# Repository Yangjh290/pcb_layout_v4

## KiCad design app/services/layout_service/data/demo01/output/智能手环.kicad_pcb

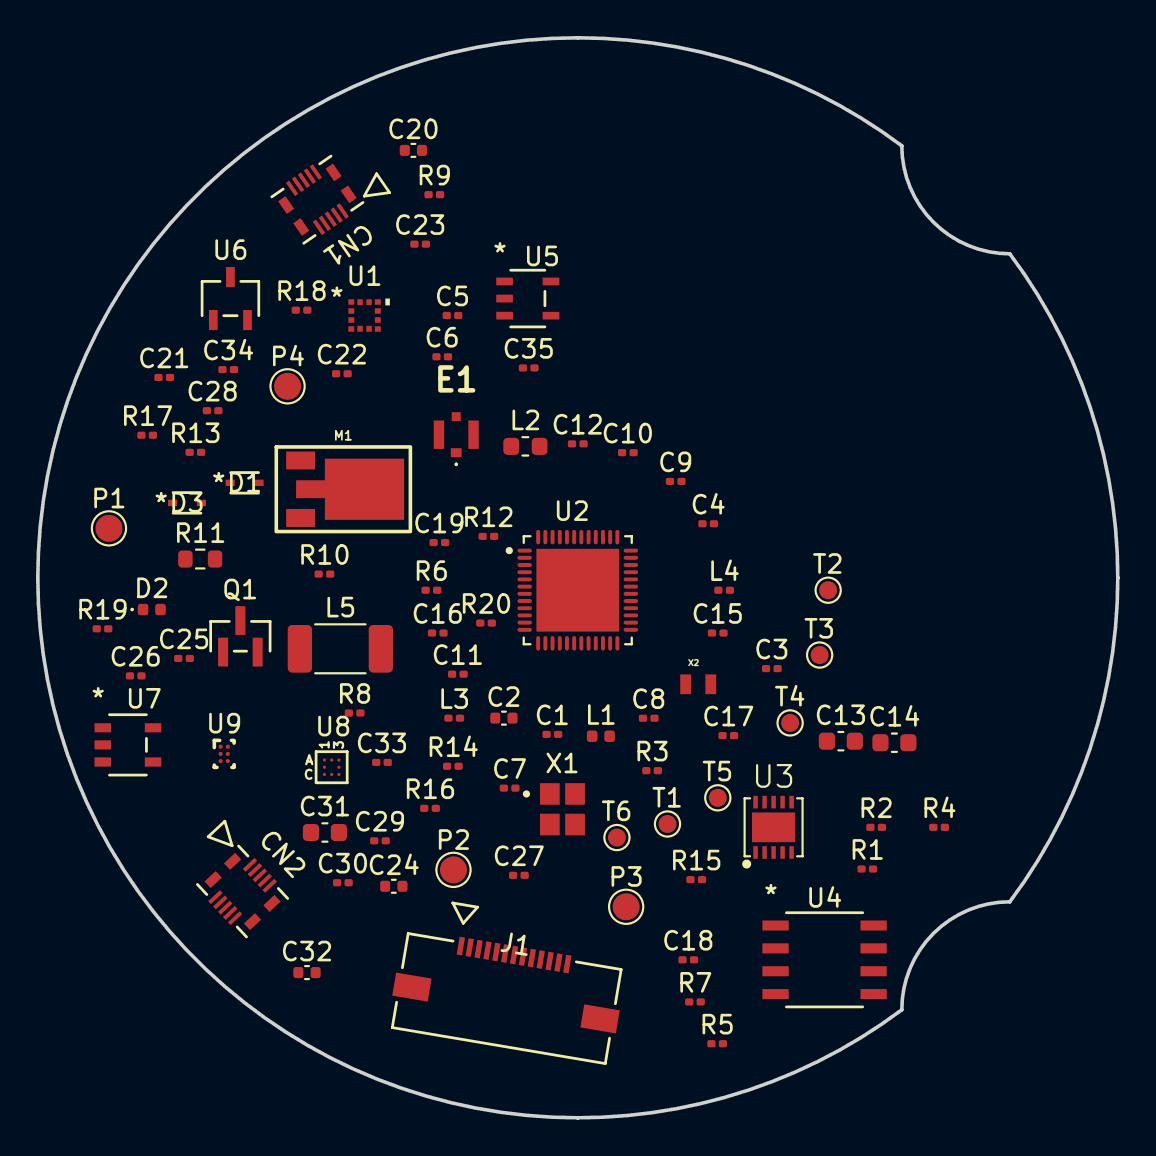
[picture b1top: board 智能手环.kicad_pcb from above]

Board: 2 copper layers, 60.0 x 60.0 mm, 90 parts (0 on the bottom side), 66 nets, no tracks yet.

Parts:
C1, C25, C29: 1uF; C_0201_0603Metric
C2, C20, C24, C32: 4.7uF; C_0402_1005Metric
C3, C5, C6, C9, C18, C19, C21, C22, C23, C26, C27, C28, C30, C33, C34, C35: 0.1uF; C_0201_0603Metric
C4, C8, C15: 12pF; C_0201_0603Metric
C7, C10: 20PF; C_0201_0603Metric
C11: 100pF; C_0201_0603Metric
C12, C17: NC; C_0201_0603Metric
C13, C14, C31: 2.2uF; C_0603_1608Metric
C16: 0.8pF; C_0201_0603Metric
CN1, CN2: CON_559099872
D1, D3: ZHCS350TA; CR_350TA_DIO
D2: BTR04F15; D_0402_1005Metric
E1: RECE.20449.001E.01; RECE20449001E01
J1: CON_5051101392_MOL
L1: 15nH; L_0402_1005Metric
L2: 10uH; L_0603_1608Metric
L3: 3.9nH; L_0201_0603Metric
L4: NC; L_0201_0603Metric
L5: LQH2MCN100M52; L_2010_5025Metric
M1: Z3OC1T8219731
P1: VUSB; TestPoint_Pad_D1.5mm
P2: B+; TestPoint_Pad_D1.5mm
P3: GND; TestPoint_Pad_D1.5mm
P4: B-; TestPoint_Pad_D1.5mm
Q1: MMBT3904; SOT-23_MCC
R1, R2, R3: 330R; R_0201_0603Metric
R4, R5, R6, R7, R8: 10K; R_0201_0603Metric
R9: NC; R_0201_0603Metric
R10: 16K_1%; R_0201_0603Metric
R11: 25.5R; R_0603_1608Metric
R12: 2K; R_0201_0603Metric
R13: 1M; R_0201_0603Metric
R14: 810K 1%; R_0201_0603Metric
R15: 155K 1%; R_0201_0603Metric
R16: 560K; R_0201_0603Metric
R17, R18, R19: 1M_1%; R_0201_0603Metric
R20: 196K_1%; R_0201_0603Metric
T1: RX; TestPoint_Pad_D1.0mm
T2: TX; TestPoint_Pad_D1.0mm
T3: SWDIO; TestPoint_Pad_D1.0mm
T4: SWDCLK; TestPoint_Pad_D1.0mm
T5: 3V3; TestPoint_Pad_D1.0mm
T6: GND; TestPoint_Pad_D1.0mm
U1: KX122_1037; LGA12_2X2_KNX
U2: NRF52832; QFN40P600X600X90-49N
U3: IQS263; IQS263B
U4: W25X40CLSNIG
U5: XC6215B332MR-G; XC6215B332MR_G
U6: XC61CC3302MR-G; XC61C_SOT-23_TOR
U7: XC6802A42XMR-G; SOP_XC6802_TOR
U8: AK09911C; WL-CSPBGA8_1p2x1p2x0p5_AKM
U9: TPS61046; YFF0006AAAA
X1: CRYSTAL1-4/SM; XTAL_FA-20H_32.0000MF12Y-W3
X2: 32.768KHz; XTAL_ECS-.327-12.5-12-TR

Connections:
3V3: C2.2, C3.2, C6.1, C13.1, C18.1, C19.2, C20.1, C21.1, C26.2, C27.2, C33.1, CN2.5, J1.4 (VDD), R4.2, R5.1, R7.1, R8.1, T5.1 (TP), U1.7 (VDD), U2.13 (VDD1), U2.36 (VDD2), U2.48 (VDD3), U3.4 (VDDHI), U4.8 (VCC), U5.5 (VOUT), U8.A1 (VDD), U8.C1 (V1.8)
AC_CLK: U1.12 (SCLK/SCL), U2.7 (P0.05/AIN3)
AC_CS#: U1.10 (nCS), U2.8 (P0.06)
AC_INT1: U1.5 (INT1), U2.10 (P0.08)
AC_MISO: U1.1 (SDO/ADDR), U2.5 (P0.03/AIN1)
AC_MOSI: U1.2 (SDI/SDA), U2.4 (P0.02/AIN0)
BAT_P: C35.1, R19.2, R20.1, U2.6 (P0.04/AIN2)
CLK: R6.1, T4.1 (TP), U2.25 (SWDCLK)
C_STATUS: R8.2, U2.17 (P0.14), U7.1 (~CHG~)
DIO: T3.1 (TP), U2.26 (SWDIO)
FLASH_CS: U2.20 (P0.17), U4.1 (~CS~)
GND: C1.1, C2.1, C3.1, C4.2, C5.2, C6.2, C7.1, C8.2, C9.2, C10.1, C11.2, C12.2, C13.2, C14.2, C16.2, C17.2, C18.2, C19.1, C20.2, C21.2, C22.1, C23.1, C24.2, C25.2, C26.1, C27.1, C29.2, C30.1, C31.2, C32.1, C33.2, C34.2, C35.2, CN1.9, CN1.10, CN2.9, CN2.10, D2.1, J1.5 (IM1), J1.12 (VSS), L4.1, M1.3 (GND), P3.1 (TP), P4.1 (TP), Q1.2 (E), R6.2, R10.2, R13.2, R15.2, R16.2, R18.2, R20.2, T6.1 (TP), U1.4 (TRIG), U1.8 (GND1), U1.9 (GND2), U2.31 (VSS1), U2.45 (VSS2), U2.49 (VSS3), U3.1 (GND), U3.11 (GND1), U4.4 (GND), U5.2 (GND), U6.2 (VSS), U7.2 (VSS), U8.B1 (VSS), U9.A2 (GND), X1.2, X1.4
HR_EN2: CN2.4, U2.21 (P0.18)
HR_INT: CN2.3, U2.22 (P0.19)
INT: U2.15 (P0.12), U8.A3 (INT)
MISO: U2.37 (P0.25), U4.2 (DO)
MOSI: J1.11 (D1), U2.38 (P0.26), U4.5 (DI)
MOTOR_DRV: R12.1, U2.14 (P0.11)
unnamed: C15.1, L3.2, L4.2
unnamed: C15.2, C17.1, E1.1
unnamed: C25.1, D1.2 (CATHODE), U7.4 (VIN)
unnamed: C28.2, D3.1 (ANODE), M1.2, Q1.3 (C)
unnamed: C28.1, D3.2 (CATHODE), M1.1, R11.2
unnamed: J1.6 (IREF), R16.1
unnamed: C32.2, J1.3 (VCOMH)
unnamed: C30.2, C31.1, J1.2 (VPP), R14.2, U9.C2 (VOUT)
unnamed: L1.2, L2.1
unnamed: Q1.1 (B), R12.2, R13.1
unnamed: C5.1, U1.3 (IO_VDD)
unnamed: C16.1, L3.1, U2.30 (ANT)
unnamed: L2.2, U2.47 (DCC)
unnamed: C9.1, U2.1 (DEC1)
unnamed: C12.1, U2.32 (DEC2)
unnamed: C11.1, U2.33 (DEC3)
unnamed: C1.2, L1.1, U2.46 (DEC4)
unnamed: C7.2, U2.2 (P0.00/XL1), X2.2
unnamed: C10.2, U2.3 (P0.01/XL2), X2.1
unnamed: C8.1, U2.34 (XC1), X1.3
unnamed: C4.1, U2.35 (XC2), X1.1
unnamed: R1.2, U3.2 (CRX1)
unnamed: R3.2, U3.3 (CRX2)
unnamed: R2.1, U3.9 (CRX3)
unnamed: C14.1, U3.5 (VREG)
unnamed: R5.2, U4.7 (~HOLD~)
unnamed: R7.2, U4.3 (~WP~)
unnamed: C23.2, R9.1, U5.3 (CE), U6.1 (VOUT)
unnamed: R10.1, U7.5 (ISEN)
unnamed: R14.1, R15.1, U9.B1 (FB)
unnamed: L5.2, U9.B2 (SW)
OLED_A0: J1.9 (DC), U2.41 (P0.29/AIN5)
OLED_CS: J1.7 (CS), U2.43 (P0.31/AIN6)
OLED_EN1: U2.16 (P0.13), U9.C1 (EN)
OLED_RES: J1.8 (RES), U2.42 (P0.30/AIN6)
POWER_UP: C34.1, R17.2, R18.1, U2.18 (P0.15)
RDY: R4.1, U2.24 (P0.21/RESET), U3.6 (RDY)
RX: T1.1 (TP), U2.28 (P0.23)
RX1: CN1.1, R1.1
RX2: CN1.2, R3.1
RX3: CN1.3, R2.2
SCL: CN2.2, U2.11 (P0.09), U3.8 (SCL), U8.B3 (SCL)
SDA: CN2.1, U2.12 (P0.10), U3.7 (SDA), U8.C3 (SDA)
SPI_CLK: J1.10 (D0), U2.39 (P0.27), U4.6 (CLK)
TX: T2.1 (TP), U2.27 (P0.22)
TX0: CN1.4, U3.10 (CTX/PO)
VBAT: C22.2, C24.1, C29.1, CN2.6, CN2.7, L5.1, P2.1 (TP), R9.2, R11.1, R19.1, U5.1 (VDD), U6.3 (VIN), U7.3 (BAT), U9.A1 (VIN)
VUSB: D1.1 (ANODE), D2.2, P1.1 (TP), R17.1

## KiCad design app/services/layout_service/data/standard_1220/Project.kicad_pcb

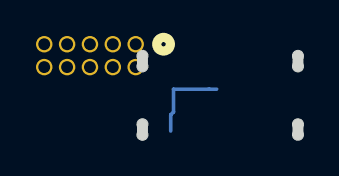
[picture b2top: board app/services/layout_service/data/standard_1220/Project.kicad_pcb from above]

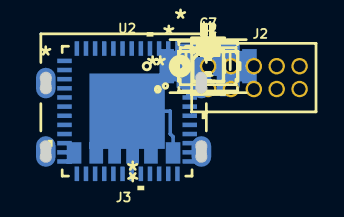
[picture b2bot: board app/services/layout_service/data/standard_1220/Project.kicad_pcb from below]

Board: 2 copper layers, 48 parts (48 on the bottom side), 25 nets.

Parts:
C1, C2: 1 uF; C_0603_1608Metric
C3: 220nF; C_0402_1005Metric
C4: 1uF; C_0402_1005Metric
C6: 0.47 uF; C_0402_1005Metric
C7: SM712-02HTG; SOT23-3_LTF
C8, C13: 10 pF; 0402C
C9, C10, C11, C15: 0.1uF; 0402C
C12, C17: 12 pF; 0402C
C14: 1uF; 0402C
C16, C18: 10uF; 0603C
D1: MMSZ5231BT1G; SOD-123_ONS
D2: PMEG3050EP,115; SDO_CFP5_SOD128_NEX
I1: STC3117IJT; BGA9C40P3X3_146X156X66
J2: M50-3500542; M50_3500542
J3: 2171750001; 2171750001_MOL
Q1: DMG2305UX-7; SOT-23_DIO
Q2: MMST3906-7-F; SOT-323_DIO
R1: 10k; R_0603_1608Metric
R2, R3: 1K; R_0402_1005Metric
R4, R5, R6: 10K; R_0402_1005Metric
R7: 10m; R_0402_1005Metric
R8, R10, R12: 10k; R_0402_1005Metric
R9: 300; R_0402_1005Metric
R11: 1k; R_0402_1005Metric
R13, R14, R15, R16: 4.7k; 0402R
R17: 1k; 0402R
R18: 330; 0402R
R19: 10k; 0402R
S1: B3U-1000P
U1: ADP122AUJZ-3.3-R7; UJ_5_ADI
U2: ATSAMD21G18A-MUT; QFN48_7X7MC_MCH
X1: 12 MHz; ABM8G_12_000MHZ_B4Y_T
X2: 32.768 kHz; ABS05_32_768KHZ_T

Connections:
+BATT: C4.1, I1.C2 (VCC), R3.1
/BATD: I1.B1 (BATD), R2.1
GND: C1.2, C2.2, C3.2, C4.2, C6.2, C7.3, C8.2, C9.2, C10.2, C11.2, C12.2, C13.2, C14.2, C15.2, C16.2, C17.2, C18.2, I1.A3 (GND), J2.3, J2.5, J3.A12 (GND), J3.B12 (GND), R7.2, R12.1, S1.1, U1.2 (GND), U2.5 (GNDANA), U2.18 (GND), U2.35 (GND), U2.42 (GND), U2.49 (EP_GND), X1.2 (GND_1), X1.4 (GND_2)
I2C_SCL: I1.B2 (SCL), R5.2, U2.22 (PA13)
I2C_SDA: I1.A2 (SDA), R6.2, U2.21 (PA12)
KLT0: J3.A5 (CC1), U2.15 (PA10)
KLT1: J3.B5 (CC2), U2.14 (PA09)
KLT2: I1.A1 (CD), U2.13 (PA08)
KLT3: I1.B3 (CS), U2.12 (PA07)
KLT4: I1.C3 (ALM), R4.2, U2.11 (PA06)
KLT5: C7.1, U2.10 (PA05)
KLT6: C7.2, C12.1, U2.1 (PA00), X2.1
unnamed: R9.1, R11.2
unnamed: D2.1 (K), Q1.3 (D), Q2.2 (EMITTER), R9.2, R10.2
unnamed: C3.1, I1.C1 (VIN), R3.2
unnamed: Q1.1 (G), R8.2
unnamed: Q2.1 (BASE), R11.1
unnamed: Q2.3 (COLLECTOR), R8.1, R10.1, R12.2
unnamed: R2.2, R7.1
unnamed: R18.2, S1.2
unnamed: R1.2, U1.3 (EN)
unnamed: C14.1, U2.43 (VDDCORE)
VBUS: J3.A9 (VBUS), J3.B9 (VBUS)
VIN0: C2.1, R1.1, U1.1 (IN)
VOUT1: C1.1, C6.1, C9.1, C10.1, C11.1, C16.1, C18.1, J2.1, Q1.2 (S), R4.1, R5.1, R6.1, R13.2, R14.2, R15.2, R16.2, R17.2, R19.2, U1.5 (OUT), U2.6 (VDDANA), U2.17 (VDDIO), U2.36 (VDDIO), U2.44 (VDDIN)

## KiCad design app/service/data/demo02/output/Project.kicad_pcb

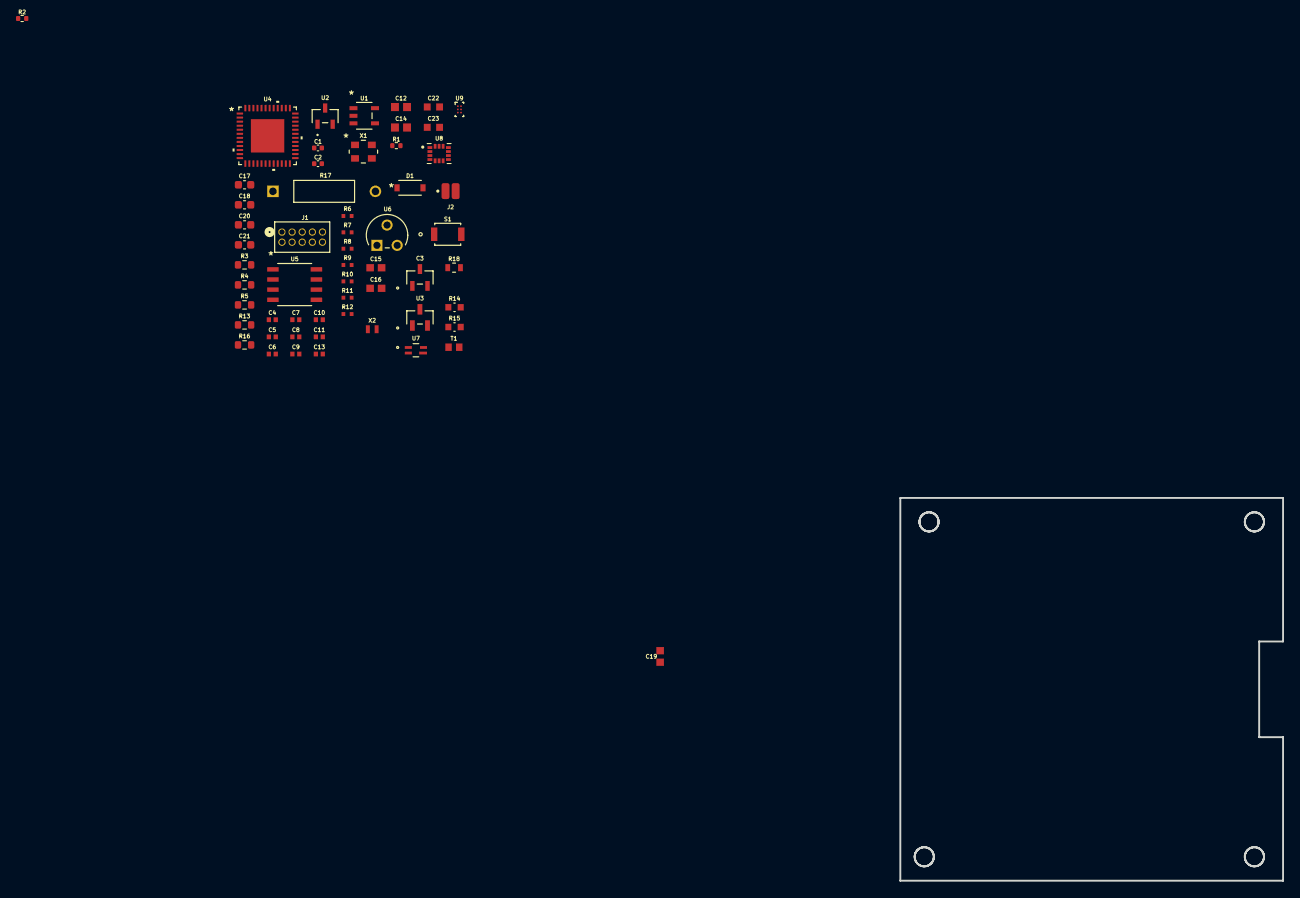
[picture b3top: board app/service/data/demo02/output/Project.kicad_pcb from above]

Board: 2 copper layers, 48.0 x 48.0 mm, 57 parts (0 on the bottom side), 27 nets, no tracks yet.

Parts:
C1, C2: 1uF; C_0402_1005Metric
C3: SM712-02HTG; SOT23-3_LTF
C4, C9: 10 pF; 0402C
C5, C6, C7, C11: 0.1uF; 0402C
C8, C13: 12 pF; 0402C
C10: 1uF; 0402C
C12, C14: 10uF; 0603C
C15, C19: 0.1uF; YAG_CC0603_YAG
C16: 0.01uF; YAG_CC0603_YAG
C17: 0.01uF; C_0603_1608Metric
C18: 1uF; C_0603_1608Metric
C20, C21: 0.1 uF; C_0603_1608Metric
C22, C23: 1uF; CAP_CL10A105KB8NNN_SAM
D1: KDZVTR6.2B; DIO_KDZLVTF100_ROM
J1: M50-3500542; M50_3500542
J2: NATTREY; SolderWirePad_1x02_SMD_1x2mm
R1: 210K; R_0402_1005Metric
R2: 40K; R_0402_1005Metric
R3: 33K; R_0603_1608Metric
R4: 1K; R_0603_1608Metric
R5: 100K; R_0603_1608Metric
R6, R7, R8, R9: 4.7k; 0402R
R10: 1k; 0402R
R11: 330; 0402R
R12: 10k; 0402R
R13: 75R; R_0603_1608Metric
R14, R15: 2.2K; RC0603N_YAG
R16: 10k; R_0603_1608Metric
R17: 6K; CMF55_VIS
R18: 1.35K; RES_RN73R_1J_KOA
S1: B3U-1000P
T1: Thermistor_NTC; TRES_NCP18XH103F03RB_MUR
U1: AP7366-W5-7; SOT25_DIO
U2: DRDC3105F-7; SOT23_MMBT2222A_NEX
U3: TCM809RVNB713; SOT-23_MC_MCH
U4: ATSAMD21G18A-MUT; QFN48_7X7MC_MCH
U5: MX25L4006EM2I-12G; SOIC8_SOP8L_MAC
U6: LM35DZ/NOPB; Z03A
U7: VEML6040A3OG; LED_VEML6040A3OG_VIS
U8: ISM330DHCXTR; PQFN50P250X300X86-14N
U9: BQ25101YFPR; YFP0006AFAV
X1: 12 MHz; ABM8G_12_000MHZ_B4Y_T
X2: 32.768 kHz; ABS05_32_768KHZ_T

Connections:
GND: C1.2, C2.2, C3.3, C4.2, C5.2, C6.2, C7.2, C8.2, C9.2, C10.2, C11.2, C12.2, C13.2, C14.2, C15.2, C16.2, C17.2, C19.2, C20.2, C21.2, C22.2, C23.2, D1.1, J1.3, J1.5, J2.2, R2.2, R3.2, R5.2, R16.2, R17.2, R18.2, S1.1, T1.2, U1.2 (GND), U2.2 (GND), U3.2 (GND), U4.5 (GNDANA), U4.18 (GND), U4.35 (GND), U4.42 (GND), U4.49 (EP_GND), U5.4 (GND), U6.3 (GND), U7.1 (GND), U8.6 (GND), U8.7 (GND), U9.C2 (VSS), X1.2 (GND_1), X1.4 (GND_2)
I2C_SCL: R9.1, R15.2, U4.26 (PA17), U7.3 (SCL), U8.13 (SCL)
I2C_SDA: R6.1, R14.2, U4.25 (PA16), U7.2 (SDA), U8.14 (SDA)
KLT0: R16.1, U4.16 (PA11), U8.4 (INT1)
KLT1: U4.15 (PA10), U8.9 (INT2)
KLT2: U4.14 (PA09), U5.5 (SI/SIO0)
KLT3: U4.13 (PA08), U5.6 (SCLK)
KLT4: U4.12 (PA07), U5.7 (HOLD#)
KLT5: C3.1, U4.11 (PA06)
KLT6: C3.2, U4.10 (PA05)
KLT7: C8.1, C18.1, U4.1 (PA00), X2.1
unnamed: C18.2, R13.2
unnamed: R3.1, R4.1, U2.1 (IN)
unnamed: R11.2, S1.2
unnamed: R1.2, R2.1, U1.4 (ADJ)
unnamed: R5.1, U3.3 (*RESET)
unnamed: C10.1, U4.43 (VDDCORE)
unnamed: R13.1, U6.2 (Vout)
unnamed: R17.1, U9.C1 (CHG_N)
unnamed: R18.1, U9.B2 (ISET)
unnamed: T1.1, U9.B1 (TS)
VDD: C19.1, R14.1, R15.1, U3.1 (VDD), U7.4 (VDD)
VIN: C22.1, U9.A2 (IN)
VOUT: C23.1, J2.1, U9.A1 (OUT)
VOUT1: C1.1, R4.2, U1.1 (IN), U1.3 (EN)
VOUT2: C2.1, R1.1, U1.5 (OUT)
VOUT3: C5.1, C6.1, C7.1, C12.1, C14.1, C15.1, C16.1, C17.1, C20.1, C21.1, D1.2, J1.1, R6.2, R7.2, R8.2, R9.2, R10.2, R12.2, U2.3 (OUT), U4.6 (VDDANA), U4.17 (VDDIO), U4.36 (VDDIO), U4.44 (VDDIN), U5.8 (VCC), U6.1 (+VS), U8.1 (SDO/SA0), U8.2 (SDX), U8.3 (SCX), U8.5 (VDDIO), U8.8 (VDD), U8.11 (SDO_AUX), U8.12 (CS)

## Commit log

2024-12-19 编写功能 生成网络和连接关系
2024-12-19 编写功能 生成网络和连接关系-2
2024-12-19 代码迁移
2024-12-20 网络和连接关系的解析
2024-12-21 fastapi-template
2024-12-23 增加修改-调用zip项目接口成功
2024-12-23 合并处理
2024-12-27 自建pcb文件
2024-12-27 自建pcb文件-2
2025-01-10 pcb板子匹配
2025-01-13 流程适配-差板子反写和坐标确定
2025-01-15 流程适配-开始考虑焊盘和旋转
2025-01-17 流程适配-开始反写网表
2025-02-12 流程适配-反写网表-v2
2025-02-17 流程适配完成-v1.0
2025-02-17 Git调试
2025-02-17 动态适配本地板子-1.0
2025-02-21 动态适配本地板子-2.0
2025-02-21 动态适配本地板子-2.1
2025-02-21 动态适配本地板子-2.2
2025-02-23 算法优化-1.0
2025-02-23 算法优化-2.0
2025-02-25 算法优化-2.1
